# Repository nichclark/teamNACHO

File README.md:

# teamNACHO
Senior Project Arduino Code

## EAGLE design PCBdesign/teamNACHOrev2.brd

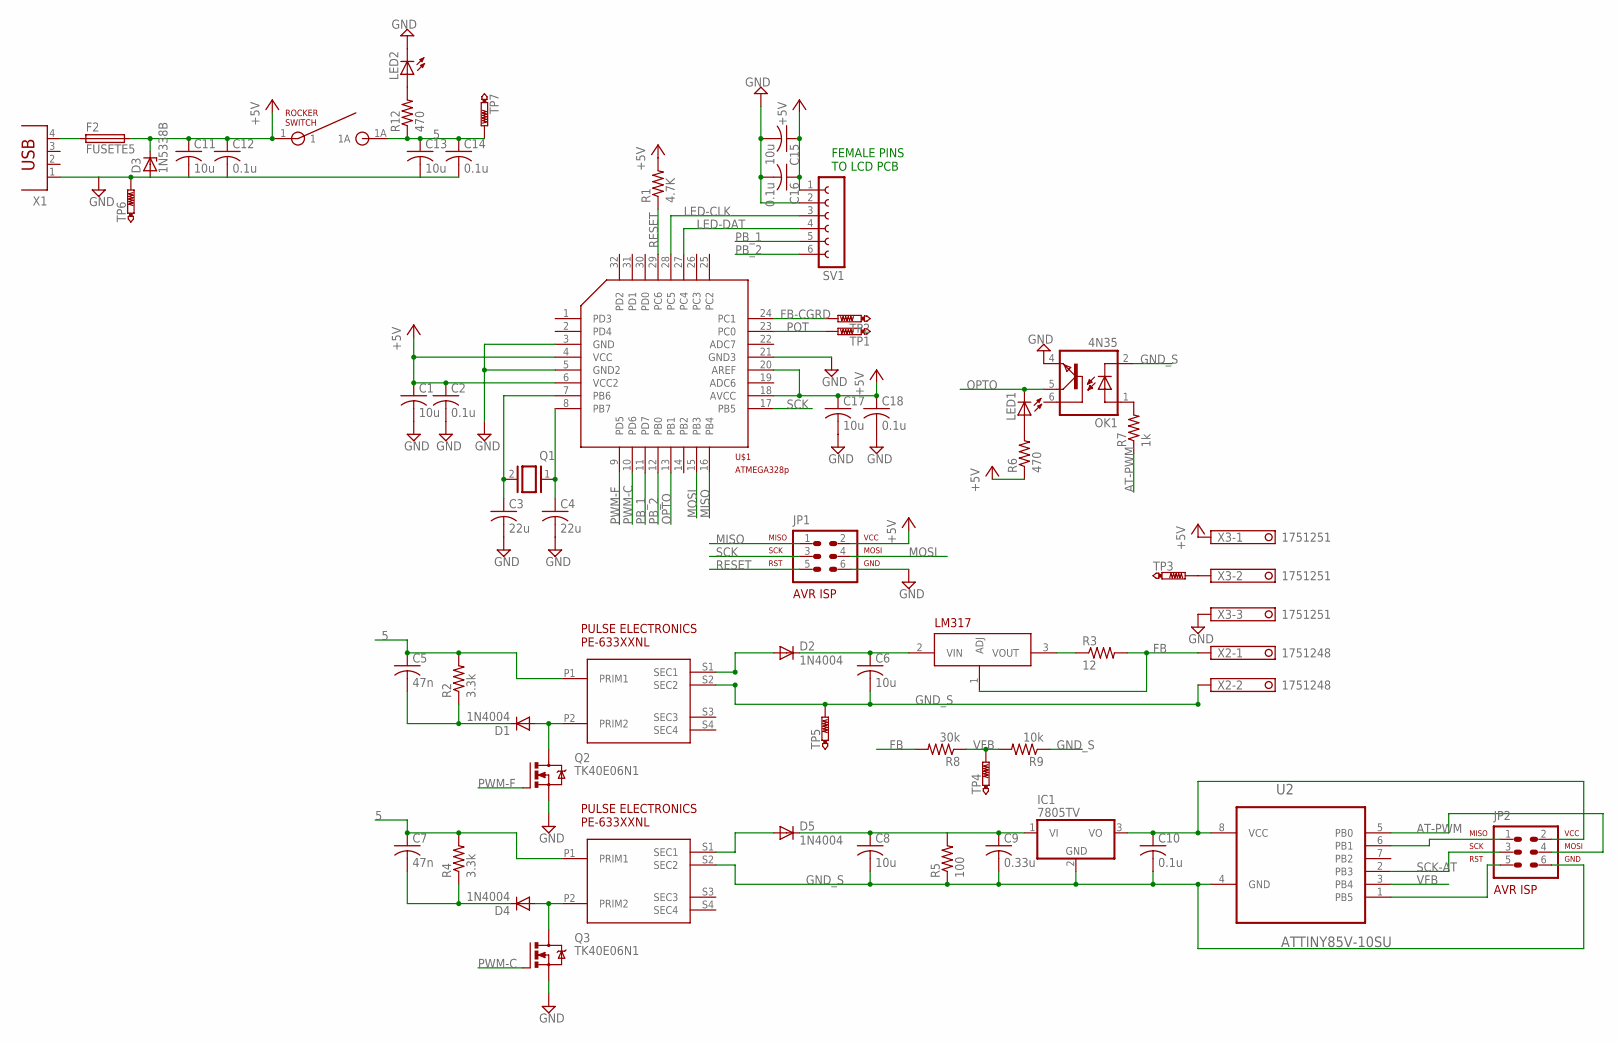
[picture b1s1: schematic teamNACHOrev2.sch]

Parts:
C1, C6, C8, C11, C13, C15, C17: 10u; C0805
C2, C10, C12, C14, C16, C18: 0.1u; C0805
C3, C4: 22u; C0805
C5, C7: 47n; C0805
C9: 0.33u; C0805
D1, D2, D4, D5: 1N4004; DO41-10
D3: 1N5338B; C1702-15
F2: FUSETE5; TE5
IC1: 7805TV; TO220V
JP1, JP2: AVR-ISP-6VERT; AVR-ISP-6
LED1, LED2: LED_ELD260; LED_LD260
OK1: 4N35; DIL06
Q1: XTAL/S; QS
Q2, Q3: TK40E06N1; TO220BV
R1: 4.7K; R0805
R2, R4: 3.3k; R0805
R3: 12; M0805
R5: 100; R0805
R6, R12: 470; M0805
R7: 1k; M0805
R8: 30k; R0805
R9: 10k; R0805
SV1: FE06-1; FE06
TP1, TP2, TP3, TP4, TP5, TP6, TP7: PTR1PAD1-20; P1-20
U2: ATTINY85V-10SU; SOIC127P798X216-8N
U$1: ATMEGA328P; TQFP32
U$2, U$5: PE-63388NL; PE-633XXNL
U$3: LM317; TO220V
U$4: COM-08837; ROCKERSWITCH
X1: PN87520
X2: 1751248
X3: 1751251

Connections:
5: C5.1, C7.1, C13.1, C14.1, R2.2, R4.2, R12.1, TP7.TP, U$2.P1 (PRIM1), U$4.1A, U$5.P1 (PRIM1)
+5V: C1.1, C2.1, C11.1, C12.1, C15.1, C16.1, C17.1, C18.1, D3.C, F2.2, JP1.2, R1.2, R6.1, SV1.1, U$1.4 (VCC), U$1.6 (VCC2), U$1.18 (AVCC), U$1.20 (AREF), U$4.1, X3.1
AT-PWM: JP2.4, R7.1, U2.5 (PB0)
FB: R3.2, R8.2, U$3.1 (ADJ), X2.1
FB-CGRD: TP2.TP, U$1.24 (PC1)
GND: C1.2, C2.2, C3.2, C4.2, C11.2, C12.2, C13.2, C14.2, C15.2, C16.2, C17.2, C18.2, D3.A, JP1.6, LED2.K (C), OK1.4 (EMI), Q2.S, Q3.S, SV1.2, TP6.TP, U$1.3 (GND), U$1.5 (GND2), U$1.21 (GND3), X1.1, X3.3
GND_S: C6.2, C8.2, C9.2, C10.2, IC1.2 (GND), JP2.6, OK1.2 (C), R5.1, R9.1, TP5.TP, U2.4 (GND), U$2.S2 (SEC2), U$5.S2 (SEC2), X2.2
LED-CLK: SV1.3, U$1.28 (PC5)
LED-DAT: SV1.4, U$1.27 (PC4)
MISO: JP1.1, U$1.16 (PB4)
MOSI: JP1.4, U$1.15 (PB3)
unnamed: C5.2, D1.C, R2.1
unnamed: C3.1, Q1.2, U$1.7 (PB6)
unnamed: C4.1, Q1.1, U$1.8 (PB7)
unnamed: D1.A, Q2.D, U$2.P2 (PRIM2)
unnamed: C8.1, C9.1, D5.C, IC1.1 (VI), R5.2
unnamed: D2.A, U$2.S1 (SEC1)
unnamed: C6.1, D2.C, U$3.2 (VIN)
unnamed: R3.1, U$3.3 (VOUT)
unnamed: LED2.A, R12.2
unnamed: LED1.A, R6.2
unnamed: TP3.TP, X3.2
unnamed: D4.A, Q3.D, U$5.P2 (PRIM2)
unnamed: C7.2, D4.C, R4.1
unnamed: D5.A, U$5.S1 (SEC1)
unnamed: C10.1, IC1.3 (VO), JP2.2, U2.8 (VCC)
unnamed: OK1.1 (A), R7.2
unnamed: JP2.5, U2.1 (PB5)
unnamed: JP2.1, U2.6 (PB1)
unnamed: F2.1, X1.4
OPTO: LED1.K (C), OK1.5 (COL), U$1.13 (PB1)
PB_1: SV1.5, U$1.11 (PD7)
PB_2: SV1.6, U$1.12 (PB0)
POT: TP1.TP, U$1.23 (PC0)
PWM-C: Q3.G, U$1.10 (PD6)
PWM-F: Q2.G, U$1.9 (PD5)
RESET: JP1.5, R1.1, U$1.29 (PC6)
SCK: JP1.3, U$1.17 (PB5)
SCK-AT: JP2.3, U2.2 (PB3)
VFB: R8.1, R9.2, TP4.TP, U2.3 (PB4)

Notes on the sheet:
FEMALE PINS TO LCD PCB

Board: 2 copper layers, 60 parts (26 on the bottom side), 40 nets, no tracks yet.

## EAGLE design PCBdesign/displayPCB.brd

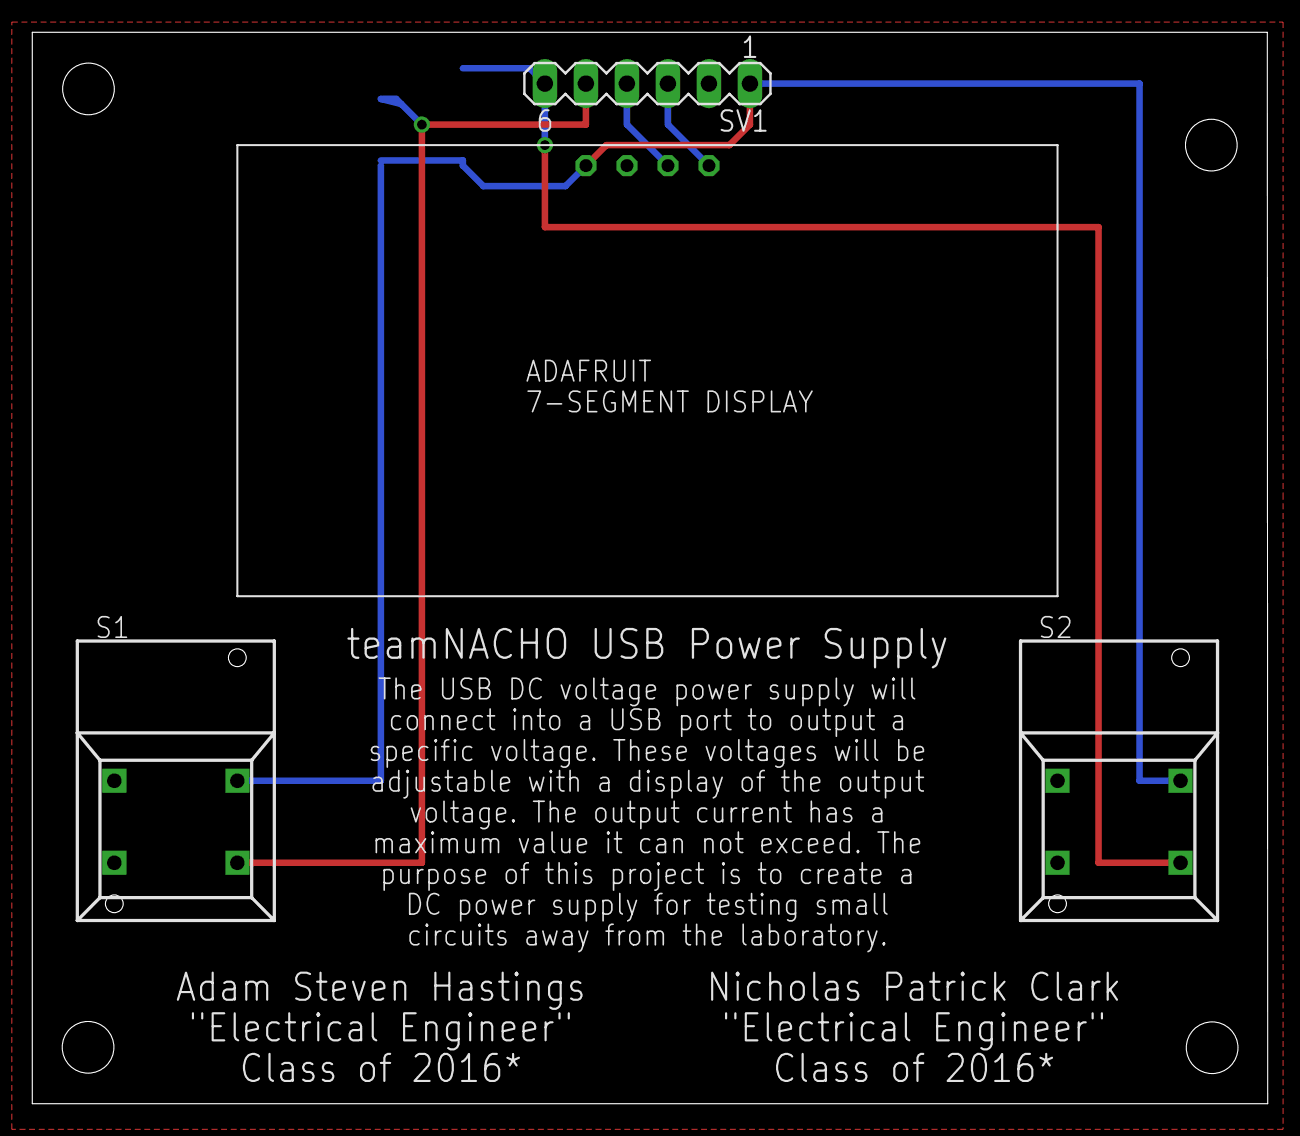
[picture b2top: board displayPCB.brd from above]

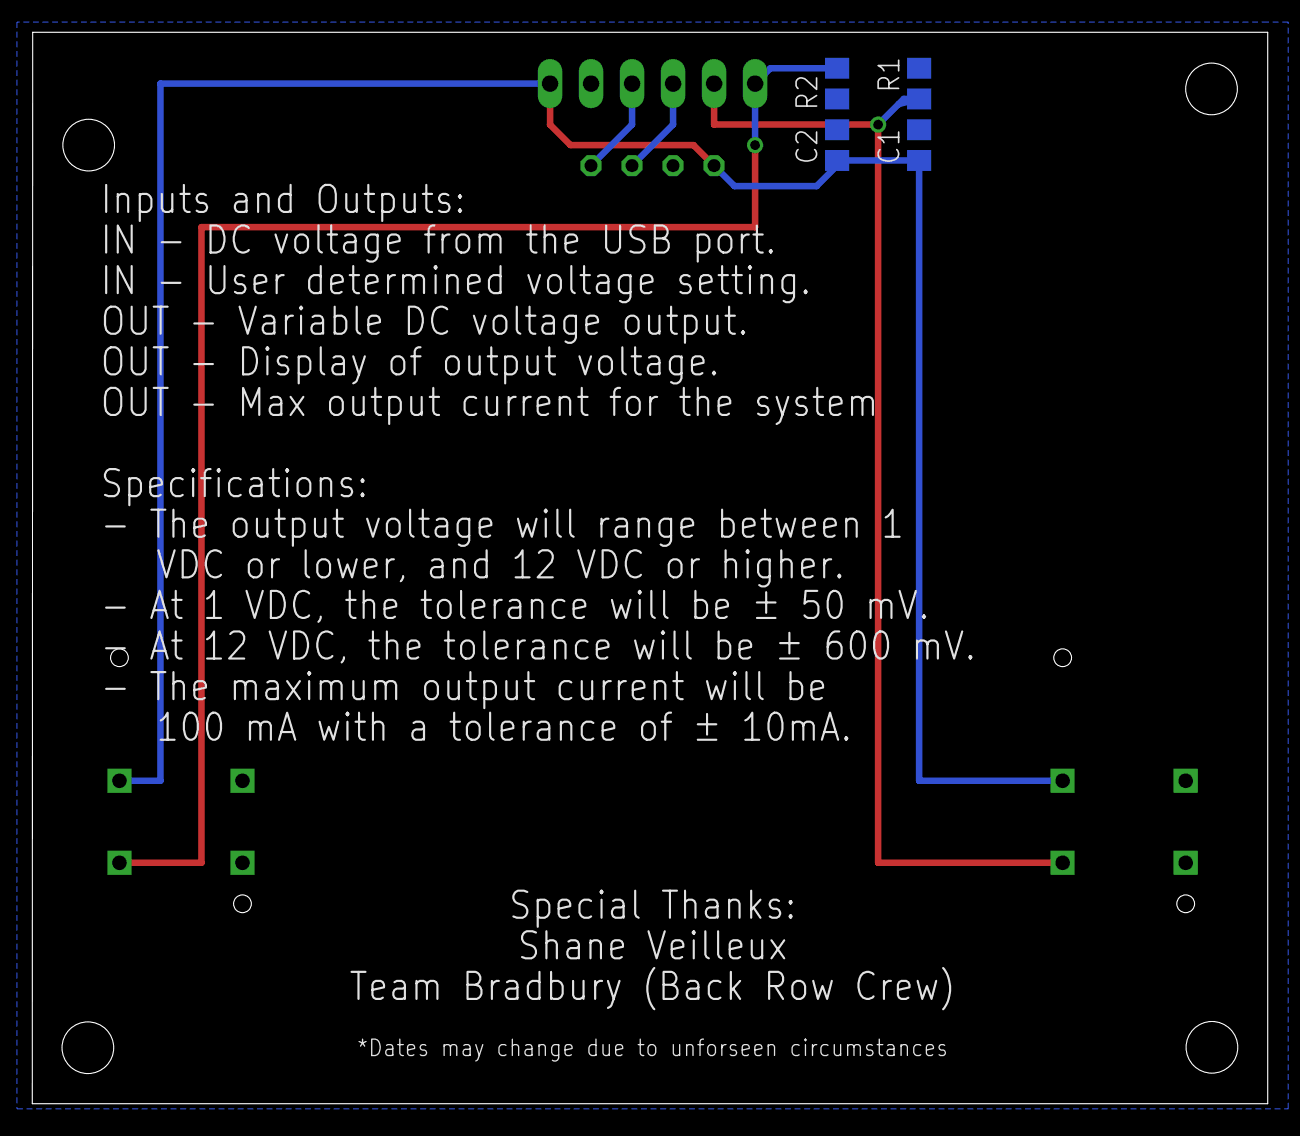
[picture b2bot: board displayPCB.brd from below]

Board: 2 copper layers, 76.5 x 66.4 mm, 8 parts (4 on the bottom side), 6 nets.

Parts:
C1: 10u; C0805
C2: 0.1u; C0805
R1, R2: 1k; R0805
S1, S2: 5501
SV1: MA06-1
U$1: AFDISPLAY

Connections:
+5V: C1.1, C2.1, S1.1A, S2.1A, SV1.1, U$1.+
GND: C1.2, C2.2, R1.2, R2.2, SV1.2, U$1.-
unnamed: SV1.3, U$1.C
unnamed: SV1.4, U$1.D
unnamed: R1.1, S1.NO, SV1.5
unnamed: R2.1, S2.NO, SV1.6

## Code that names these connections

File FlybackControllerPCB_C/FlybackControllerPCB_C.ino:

/* TeamNACHO's "NACHO Power" USB Power Supply- CGrade Code
 *  By: Nicholas Clark & Adam Hastings
 *  Date Complete: 07 December 2015
 *  
 *  Pins being used for CGrade PCB on ATmega328p:
 *  PC5-7seg display/CLK = A5
 *  PC4-7seg display/DAT = A4
 *  PC1-Feedback = A1
 *  PD5-PWM = D5
 *  PD7-Pushbutton1 = D7
 *  PB0-Pushbutton2 = D8
 *  
 */
#include <Wire.h>
#include "Adafruit_LEDBackpack.h"
#include "Adafruit_GFX.h"
Adafruit_7segment matrix = Adafruit_7segment();

#define maxValue 1250
#define minValue 50

// These variables correspond to pins on the Arduino
int PWMOutput = 5;
int pot = A0;
int feedback = A1;
// These global variables are initialized and set to zero
long LastTime = 0;
int OutputSignal = 0;
int Last = 0;
int Integral = 0;
int DutyCycle = 0;
int Error = 0;
int P = 0;
int I = 0;
int D = 0;
int Duty = 0;
int Actual = 0;
int Desired = 0;
int button = 7;
int button2 = 8;
int bounceTime = 50;
int holdTime = 2500;
int x=0;

int lastReading = HIGH;
int lastReading2 = HIGH;

int hold = 0;
int hold2 = 0;

int single = 0;
int single2 = 0;

long onTime = 0;
long lastSwitchTime = 0;


//The follow varables are what get used in the PID loop
int kP = 0.2; //proportional constant
int kI = 1; //integral constant
int kD = 0; //derivative constant
int IntegralRange = 500; //sets when the intergral term start taking effect
long SampleTime = 50; //how often PID loop runs in miliseconds

void setup() {
  //TCCR0B is the internal clock the program uses. The default scale 
  //factor for this clock is 0x04, making the clock frequency 976.5625 Hz.
  //By changing the scale factor to 0x01, the new clock frequency is
  //62500 Hz. This change in clock speed had to be done so that the output
  //pin, pin6, would be at 62.5kHz. This information is from
  //http://playground.arduino.cc/Main/TimerPWMCheatsheet
  TCCR0B = (TCCR0B & 0b11111000) | 0x01;
  Serial.begin(9600); //Baud rate of serial monitor used for debugging
  matrix.begin(0x70);
  pinMode(5,OUTPUT);
  pinMode(7,INPUT);
  pinMode(8,INPUT);
  pinMode(A1,INPUT);
}

void loop() {
  long CurrentTime = millis()/64;
  Desired = userInput();
  Actual = analogRead(feedback); 

  if(CurrentTime - LastTime > SampleTime){
    Error = Desired - Actual;
    if(abs(Error) < IntegralRange) Integral = Integral + Error;
    else Integral = 0;
    P = Error * kP;
    I = Integral * kI;
    D = (Last - Actual) * kD;
    Duty = P + I + D;
    if(Duty > 1000) Duty = 1000;
    if(Duty < 0) Duty = 0; 
    DutyCycle = map(Duty, 0, 1024, 0, 255); 
    Last = Actual;
    LastTime = CurrentTime;

    Serial.print("Error equals ");
    Serial.print(Error);Serial.print(", ");
    Serial.print("Output Duty = ");
    Serial.print(Duty);Serial.print(", ");
    Serial.println(DutyCycle);
  }
  analogWrite(PWMOutput, 125);
  displayValue(Desired);
  
}
void displayValue (int value){
  int A;int B;int C;int D;
  //value will have a max value of 1250
  //value = map(value,0,1024,minValue,maxValue);
  A = value/1000;
  B = (value/100) - (A*10);
  C = (value/10) - (A*100) - (B*10);
  D = (value/1) - (A*1000) - (B*100) - (C*10);
  
  matrix.writeDigitNum(0,A);
  matrix.writeDigitNum(1,B,true);
  matrix.writeDigitNum(3,C);
  matrix.writeDigitNum(4,D);
  matrix.writeDisplay();
}

int userInput(){
  int reading = digitalRead(button);
  int reading2 = digitalRead(button2);

  //first pressed
  if (reading == LOW && lastReading == HIGH && reading2 == HIGH) {
    onTime = millis();
    x=x+10;
  }
  
  //held
  if (reading == LOW && lastReading == LOW && reading2 == HIGH) {
    if ((millis() - onTime) > holdTime) {
      x=x+10;
      hold = 1;
    }
  }
  
  //released
  if (reading == HIGH && lastReading == LOW) {
    if (hold == 1) hold = 0;
  }
  
  lastReading = reading;
  
  //DECREMENT SETUP
  
  
  //first pressed
  if (reading2 == LOW && lastReading2 == HIGH && reading == HIGH) {
    onTime = millis();
    x=x-10;
  }
  
  //held
  if (reading2 == LOW && lastReading2 == LOW && reading == HIGH) {
    if ((millis() - onTime) > holdTime) {
      x=x-10;
      hold2 = 1;
    }
  }
  
  //released
  if (reading2 == HIGH && lastReading2 == LOW) {
    if (hold2 == 1) hold2 = 0;
  }
  if(x > maxValue) x = maxValue;
  if(x < minValue) x = minValue;
  lastReading2 = reading2;
  //x = map(x,minValue,maxValue,0,1024);
  return x;
}

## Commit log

2015-10-23 Testing GitHub from MacBook
2015-10-23 Testing the analogWrite function
2015-10-23 Initial start to the PID loop
2015-10-23 Shaun communication test
2015-10-23 First attempt at complete PI Loop
    Used code to drive a DC fan. Used a pot to set the desired speed.
2015-10-26 Redid PID loop program, have not tested yet
2015-10-26 Started to break code into subroutines for debugging
2015-10-26 Went back to the first PID loop controller, new one wasn't working
2015-10-27 Program Works!!
    At this point, the program is able to drive the circuit. Changed the kP
    and kI values to try to get a steady response, but still not perfect.
    Need to play around with values more. Maybe add a kD term to code?
2015-10-27 Added kD and subroutine
    Move PID loop into subroutine to make main loop simpler. Also added
    derivative term calculations to program. Hopefully this will help reduce
    SSE.
2015-10-29 PID coeffs
    got PID coefficients closer to ideal. this reduced the ripple on the
    output greatly.
2015-11-02 7-seg display
    Started to mess around with 7-seg display, had to download libraries
    from Adafruit to be able to implement with board.
    https://learn.adafruit.com/adafruit-led-backpack/0-dot-56-seven-segment-backpack
2015-11-02 UI for increasing and decreasing output voltage.
    added push buttons to 7-segment display circuit. trying to make the
    segment increment and decrement when either button is pressed.
2015-11-02 button pressed testing
    got the value on the display to increment, debounce doesnt work......
2015-11-02 changed stuff
    value increases and decreases now. when both are pressed, nothing
    happens.
2015-11-02 PCB design Rev1
    Started to do PCB schematic. Got ATmega328p library from Shaun.
2015-11-03 still working on PB
    got the counter to increment by only 1 each time a button is pressed.
2015-11-03 ATmega
    Believe the initial set up of atmega328p has been done.
2015-11-03 PB stuff still
    made it so when either button is pressed and held, the other will not
    work.
2015-11-03 Transformer Added
    Created and added the transformer to circuit. Started to create flyback
    circuit.
2015-11-03 Created PE-63388NL Library item
2015-11-03 push and hold PB
    got the buttons to increment & decrement by 1 with one press and
    increment/decrement rapidly with a hold.
2015-11-04 Slowly but surely
    Slowly adding more components to schematic. still not sure how to do
    atmega correctly
2015-11-04 PCB Board Layout
    Started to lay out the board
2015-11-04 Fixed USB
    Flipped which pins on USB are ground and power. Also may have to make
    own lib for LM317, they don’t have the correct pcb package we need.
2015-11-04 Cleaned Up Code
    Created subroutines so that one routine controls PB logic and
    incrementing a value. A limit of the value was created to represent the
    limits of our circuits capabilities. The other subroutine then posts the
    value to the display. To get the decimal, a colon was used. To actually
    get the decimal, we are going to have to do a lot more programming, may
    not be worth it to us to do.
2015-11-04 Tried using PBs
    Not sucessfull, can't convert display number into ADC range properly
2015-11-09 ATtiny Program
    Decided to use an ATtiny85 to take the output voltage and create a
    signal. The signal will pass through an opto. This will allow us to have
    isolation between the two sides of the circuit. Right now it takes the
    voltage to control a duty cycle, may have it control frequency instead?
    Not sure yet.
2015-11-09 added reading PWM duty cycle
    was able to read the duty cycle that was being output from the
    optocoupler. getting close to isolation!!!!!!!!!!!!!!!
2015-11-11 Added Opto Code
    Added the DutyCycle reading code and created a few subroutines. Now
    there is no analog to digital readings happening in the code.
2015-11-12 PCB design Rev 1
2015-11-12 something aint right
    yeah...... it doesnt work.... going backwards
2015-11-12 test
    git hub is making me do this for some reason
2015-11-13 hur ya go
    asdfasdf
2015-11-13 HERE YOU GO ADAM
2015-11-16 Done with PCB Rev1 for Power Supply and Display PCB
2015-11-17 trying to get font to fit
2015-11-17 designPCB complete
    PCB complete and uploaded to OSHpark for ordering
2015-11-18 Started to create header files
2015-11-18 Moved some subroutines into header files
2015-12-04 Didn't realize we can make revs on this........
    Well fuck
2015-12-04 PCB Program
    This program is the program that will be/is on the PCB. It has the
    correct pins for the atmega328p
2015-12-05 Created a C-Grade program
    Since PCB is not working, created a new file that will be used strictly
    for the C-grade circuit. The program has bare minimums to get circuit
    to meet teachers expectations. So far, have fixed the PID loop
    interrupt issue. However, PID loop is not working, for some reason it
    is just taking the calculated Error and setting that as the output duty
    cycle.
2015-12-06 Got PID controller to Work at 1V
    Was able to get PID constants to work at 1V. Decided that to meet
    contract spec, will need to have different sets of PID constants for
    the range of output voltages circuit can reach. That is the next step.
2015-12-06 PID Controller Constants
    Now have a set of constants that will work at 1V and 5V. For some
    reason when I try to get up to 12V, the program gets stuck at the max
    duty cycle allowed. Also have to hit reset button every time load
    resistor is changed, output is not going back down to zero.
2015-12-06 Progress
    Still trying to figure out coeffs for 12V. Think that code will work
    better when PBs are used instead of pot
2015-12-06 Don't need the D
    Realized that the D term was screwing up the code. Was able to get 12V
    now. However, now can’t get 1V
2015-12-06 May have solved issue
    When I had issues before, was using a load resistor of 5kohm. Replaced
    with a 200ohm and was able to get regulated voltage at 1V and 12V.
    Think this means we need to determine what the max and min load we can
    drive.
2015-12-07 Comments complete for CGrade Code
    Comments Done.
2015-12-07 Above and Beyond Circuit
    This program will be used for above&beyond perf board circuit.
2015-12-07 Header files!
    All subroutines have now been put into header files
2015-12-07 Initializations
    Added the initialization of the clock and the serial monitor
2015-12-07 Display
    Instead of calculating the user input and displaying it in one header
    file, it is now in seperate
2015-12-07 Feedback
    This header file reads a digital pin and determines what the duty cycle
    is. This is how the feedback of the output voltage is determined
2015-12-07 User Input
    This header file uses the PBs to determine what the user desired output
    voltage will be
2015-12-07 PID control
    This header file gets passed the variables for the PID loop. It also is
    the code from the CGrade program.
2015-12-08 Most of the way done
    At this point, all of the necessary code is in header files that are
    being included. Also have changed to using an interrupt fxn to run the
    PID loop instead of trying to do it on our own. As of right now, the
    PID loop, initializations, feedback calc, and user input are in their
    own header files. Writing to the display had to be done as a subroutine
    as a matrix had to be declared. The initializations and writing to
2015-12-08 New Inits
    At this point, the clock has been initialized differently. This was due
    to the need to initialize an interrupt. The modes of all the arduino
    pins is also initialized now.
2015-12-08 New PID debug
    Added some extra lines for debugging to serial monitor. Also moved the
    Actual and Desired values to global variables for other header files to
    use.
2015-12-08 New PBs
    Moved the max and min values to global variables for other header files.
    Also had to change how PBs are read as the buttons are normally closed
    instead of normally open. As of right now, not able to get code to work
    properly.
2015-12-08 Changed variable name
    Changed variable name of "feedback" to "Vopto" to lessen confusion.
    Feedback as variables was being used too much in code.
2015-12-08 Don't need anymore
    Don't need header file anymore since matrix had to be declared in main
    code. However, was able to get decimal to print by calculating what
    digit needed to be displayed for each 7seg. This code is now all in the
    main code.
2015-12-08 Started making a second pcb board just in case
2015-12-08 Changed what pin on ATtiny85 reads Vopto
2015-12-10 Had to tell ATtiny what voltage to reference
2015-12-10 Have been using this code to try to debug circuit
2015-12-11 CGrade code next step
    This program uses CGrade hardware, but will use a 7seg w/PBs to set
    desired value instead of pot
2015-12-12 This code will be PCB code for non-isolated grounds
    This has correct pin outs
2015-12-13 got feed back working
    The feedback was working on another arduino. the problem we were having
    is that the timer was changed in order to produce a 62.5K Hz pwm for the
    mosfets.
2015-12-13 Meshing two PCBs together
    Trying to get the 7seg/PB pcb to work with CGrade circuit pcb. Using a
    desired value that is on 7seg is not working well in PID loop.
2015-12-14 got feedback PWM to be read.
    read the length in time the feedback signal was low.
2015-12-14 Feedback included with code
    This code now has code to read PWM input to calculate duty cycle. For
    some reason subroutines and header files are not working correctly. As
    of right now, are code is in main loop. Once program works, will try to
    recreate subroutines, get rid of global variables, etc.
2015-12-14 Tried new comparator circuit
    We got the new comparator circuit to work with the arduino powered off
    the same USB as the input power. Also got push buttons to work with the
    PI loop.
2015-12-15 IT WORKS!!!!!!
    Hummels figured out our circuit problem, which made the code way easier
    to measure the duty cycle. Now we are trying to get rid of all the
    global variables and create subroutines. 2 days left.
2015-12-16 Continued moving forward
    Continued to make progress on reorganizing and the PID loop. The PID
    loop is not working correctly at the moment, going to do research and
    try to figure out if better way to calculate terms.
2015-12-16 What comes first, the chicken or the egg?
    Can get the calculate feedback fxn if set duty cycle is on analogWrite.
    Can’t get any readings if use PID loop…must be missing something in the
    code that is creating this issue, maybe a timing issue?
2015-12-16 PID works!
    Adam realized that our max output duty we were allowing was too large,
    it was not letting the circuit discharge fast enough. So we changed the
    max allowable duty cycle from 97% to 78%. Had to pull some terms out of
    the subroutines and make them global variables to make it work.
2015-12-16 PID close to done
    Have got the PID coeffs close to correct. Time to start moving
    subroutines into header files
2015-12-16 PID Header file complete
    Copied subroutine over.
2015-12-16 Inits Header file complete
    Copied over code from setup loop. Had to leave matrix communication as
    the display subroutine is staying in main code.
2015-12-16 Forgot to remove the Switch, not using anymore
2015-12-16 Feedback Header file complete
    Copied subroutine over to header file.
2015-12-17 Comments are dun and IMPLEMENTED.
